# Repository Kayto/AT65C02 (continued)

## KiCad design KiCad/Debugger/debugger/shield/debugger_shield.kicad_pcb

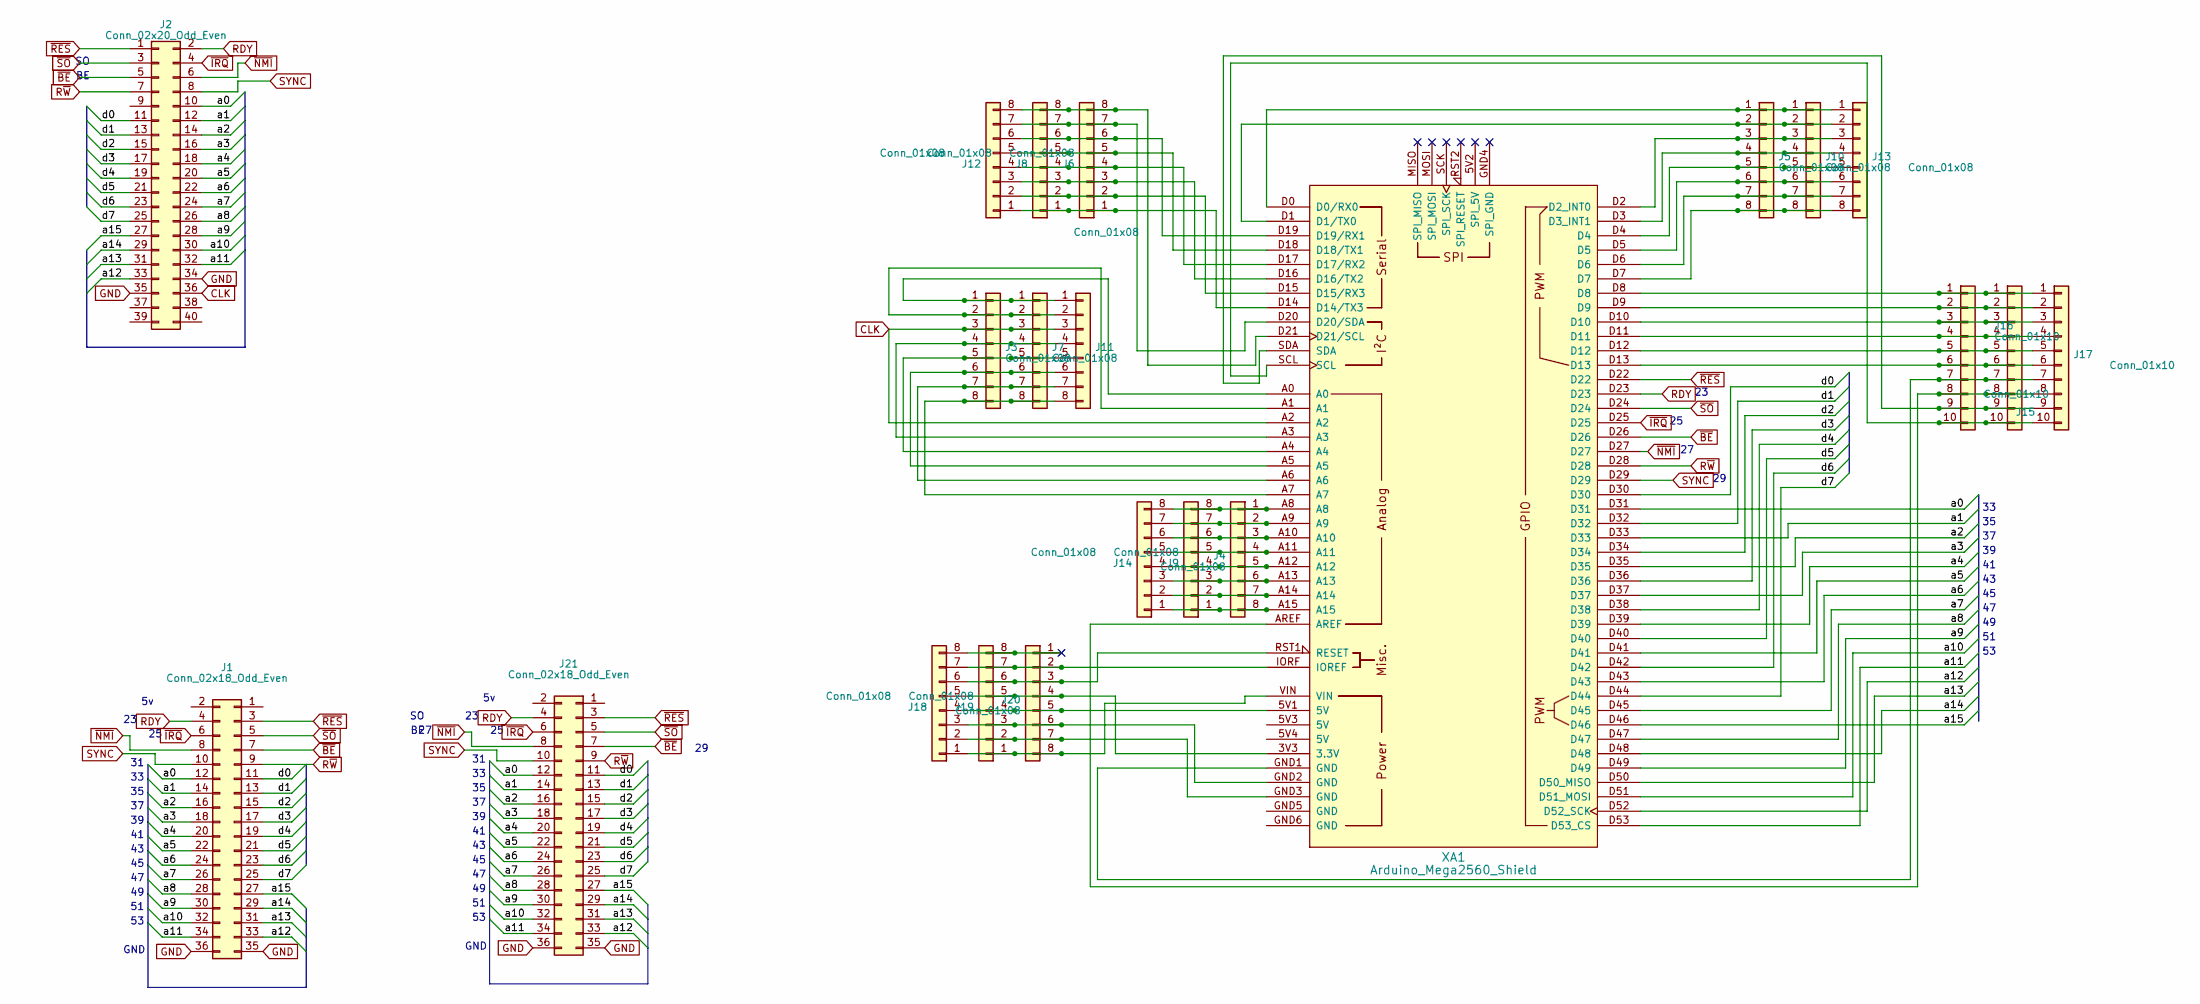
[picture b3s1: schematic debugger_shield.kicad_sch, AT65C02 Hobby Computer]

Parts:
J1: Conn_02x18_Odd_Even; PinHeader_2x18_P2.54mm_Vertical
J2: Conn_02x20_Odd_Even; IDC-Header_2x20_P2.54mm_Vertical
J3, J4, J5, J6, J11, J12, J13, J14, J18, J20: Conn_01x08; PinHeader_1x08_P2.54mm_Vertical
J7, J8, J9, J10, J19: Conn_01x08; PinSocket_1x08_P2.54mm_Vertical
J15, J17: Conn_01x10; PinHeader_1x10_P2.54mm_Vertical
J16: Conn_01x10; PinSocket_1x10_P2.54mm_Vertical
J21: Conn_02x18_Odd_Even; PinSocket_2x18_P2.54mm_Vertical
XA1: Arduino_Mega2560_Shield

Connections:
/a0: J1.12, J2.10, J21.12, XA1.D31
/a1: J1.14, J2.12, J21.14, XA1.D33
/a2: J1.16, J2.14, J21.16, XA1.D35
/a3: J1.18, J2.16, J21.18, XA1.D37
/a4: J1.20, J2.18, J21.20, XA1.D39
/a5: J1.22, J2.20, J21.22, XA1.D41
/a6: J1.24, J2.22, J21.24, XA1.D43
/a7: J1.26, J2.24, J21.26, XA1.D45
/a8: J1.28, J2.26, J21.28, XA1.D47
/a9: J1.30, J2.28, J21.30, XA1.D49
/a10: J1.32, J2.30, J21.32, XA1.D51 (D51_MOSI)
/a11: J1.34, J2.32, J21.34, XA1.D53 (D53_CS)
/a12: J1.33, J2.33, J21.33, XA1.D52 (D52_SCK)
/a13: J1.31, J2.31, J21.31, XA1.D50 (D50_MISO)
/a14: J1.29, J2.29, J21.29, XA1.D48
/a15: J1.27, J2.27, J21.27, XA1.D46
/d0: J1.11, J2.11, J21.11, XA1.D30
/d1: J1.13, J2.13, J21.13, XA1.D32
/d2: J1.15, J2.15, J21.15, XA1.D34
/d3: J1.17, J2.17, J21.17, XA1.D36
/d4: J1.19, J2.19, J21.19, XA1.D38
/d5: J1.21, J2.21, J21.21, XA1.D40
/d6: J1.23, J2.23, J21.23, XA1.D42
/d7: J1.25, J2.25, J21.25, XA1.D44
CLK: J2.36, J3.3, J7.3, J11.3, XA1.A2
GND: J1.35, J1.36, J2.34, J2.35, J21.35, J21.36
unnamed: J5.1, J10.1, J13.1, XA1.D0 (D0/RX0)
unnamed: J5.2, J10.2, J13.2, XA1.D1 (D1/TX0)
unnamed: J5.3, J10.3, J13.3, XA1.D2 (D2_INT0)
unnamed: J5.4, J10.4, J13.4, XA1.D3 (D3_INT1)
unnamed: J5.5, J10.5, J13.5, XA1.D4
unnamed: J5.6, J10.6, J13.6, XA1.D5
unnamed: J5.7, J10.7, J13.7, XA1.D6
unnamed: J5.8, J10.8, J13.8, XA1.D7
unnamed: J3.1, J7.1, J11.1, XA1.A0
unnamed: J3.2, J7.2, J11.2, XA1.A1
unnamed: J3.4, J7.4, J11.4, XA1.A3
unnamed: J3.5, J7.5, J11.5, XA1.A4
unnamed: J3.6, J7.6, J11.6, XA1.A5
unnamed: J3.7, J7.7, J11.7, XA1.A6
unnamed: J3.8, J7.8, J11.8, XA1.A7
unnamed: J6.1, J8.1, J12.1, XA1.D14 (D14/TX3)
unnamed: J6.2, J8.2, J12.2, XA1.D15 (D15/RX3)
unnamed: J6.3, J8.3, J12.3, XA1.D16 (D16/TX2)
unnamed: J6.4, J8.4, J12.4, XA1.D17 (D17/RX2)
unnamed: J6.5, J8.5, J12.5, XA1.D18 (D18/TX1)
unnamed: J6.6, J8.6, J12.6, XA1.D19 (D19/RX1)
unnamed: J6.7, J8.7, J12.7, XA1.D20 (D20/SDA)
unnamed: J6.8, J8.8, J12.8, XA1.D21 (D21/SCL)
unnamed: J4.8, J9.1, J14.1, XA1.A15
unnamed: J4.7, J9.2, J14.2, XA1.A14
unnamed: J4.6, J9.3, J14.3, XA1.A13
unnamed: J4.5, J9.4, J14.4, XA1.A12
unnamed: J4.4, J9.5, J14.5, XA1.A11
unnamed: J4.3, J9.6, J14.6, XA1.A10
unnamed: J4.2, J9.7, J14.7, XA1.A9
unnamed: J4.1, J9.8, J14.8, XA1.A8
unnamed: J15.1, J16.1, J17.1, XA1.D8
unnamed: J15.2, J16.2, J17.2, XA1.D9
unnamed: J15.3, J16.3, J17.3, XA1.D10
unnamed: J15.4, J16.4, J17.4, XA1.D11
unnamed: J15.5, J16.5, J17.5, XA1.D12
unnamed: J15.6, J16.6, J17.6, XA1.D13
unnamed: J15.7, J16.7, J17.7, XA1.GND1 (GND)
unnamed: J15.8, J16.8, J17.8, XA1.AREF
unnamed: J15.9, J16.9, J17.9, XA1.SDA
unnamed: J15.10, J16.10, J17.10, XA1.SCL
unnamed: J18.1, J19.1, J20.8, XA1.VIN
unnamed: J18.2, J19.2, J20.7, XA1.GND3 (GND)
unnamed: J18.3, J19.3, J20.6, XA1.GND2 (GND)
unnamed: J18.4, J19.4, J20.5, XA1.5V1 (5V)
unnamed: J18.5, J19.5, J20.4, XA1.3V3 (3.3V)
unnamed: J18.6, J19.6, J20.3, XA1.RST1 (RESET)
unnamed: J18.7, J19.7, J20.2, XA1.IORF (IOREF)
RDY: J1.4, J2.2, J21.4, XA1.D23
R~W: J1.9, J2.7, J21.9, XA1.D28
SYNC: J1.10, J2.8, J21.10, XA1.D29
~BE: J1.7, J2.5, J21.7, XA1.D26
~IRQ: J1.6, J2.4, J21.6, XA1.D25
~NMI: J1.8, J2.6, J21.8, XA1.D27
~RES: J1.3, J2.1, J21.3, XA1.D22
~SO: J1.5, J2.3, J21.5, XA1.D24

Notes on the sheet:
GND

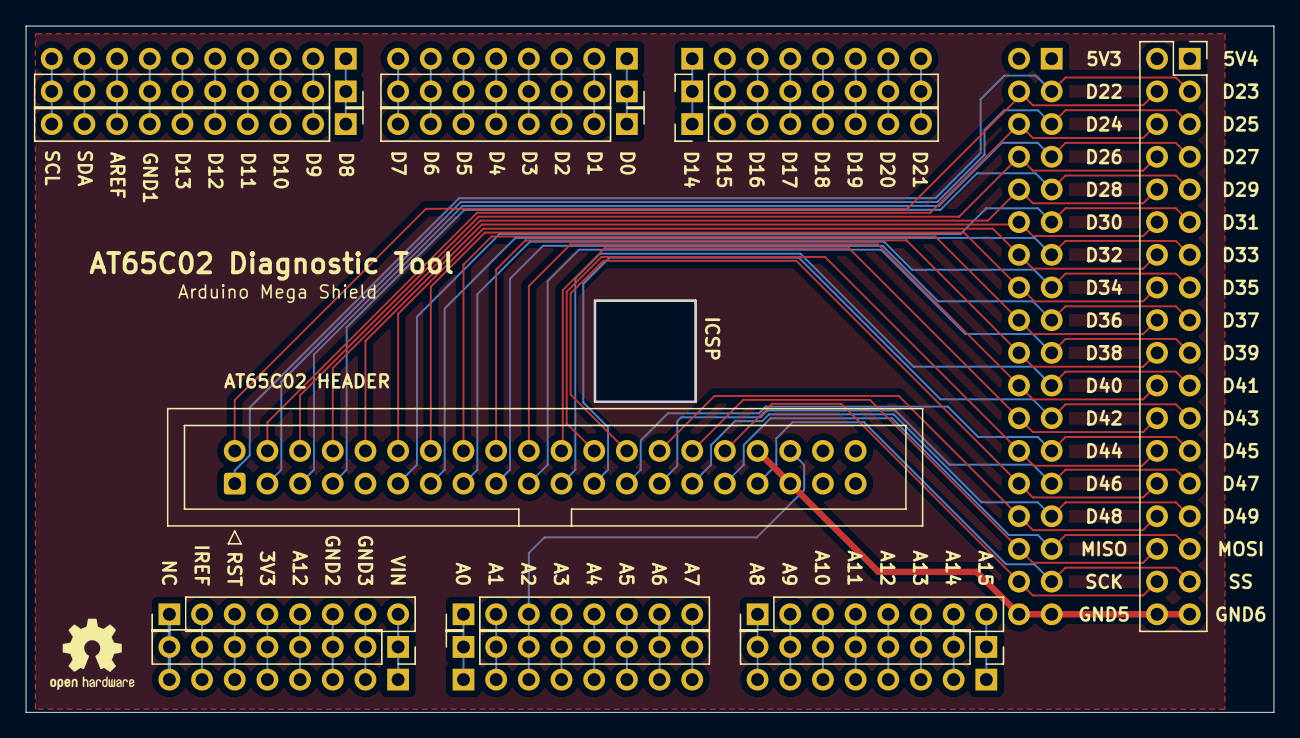
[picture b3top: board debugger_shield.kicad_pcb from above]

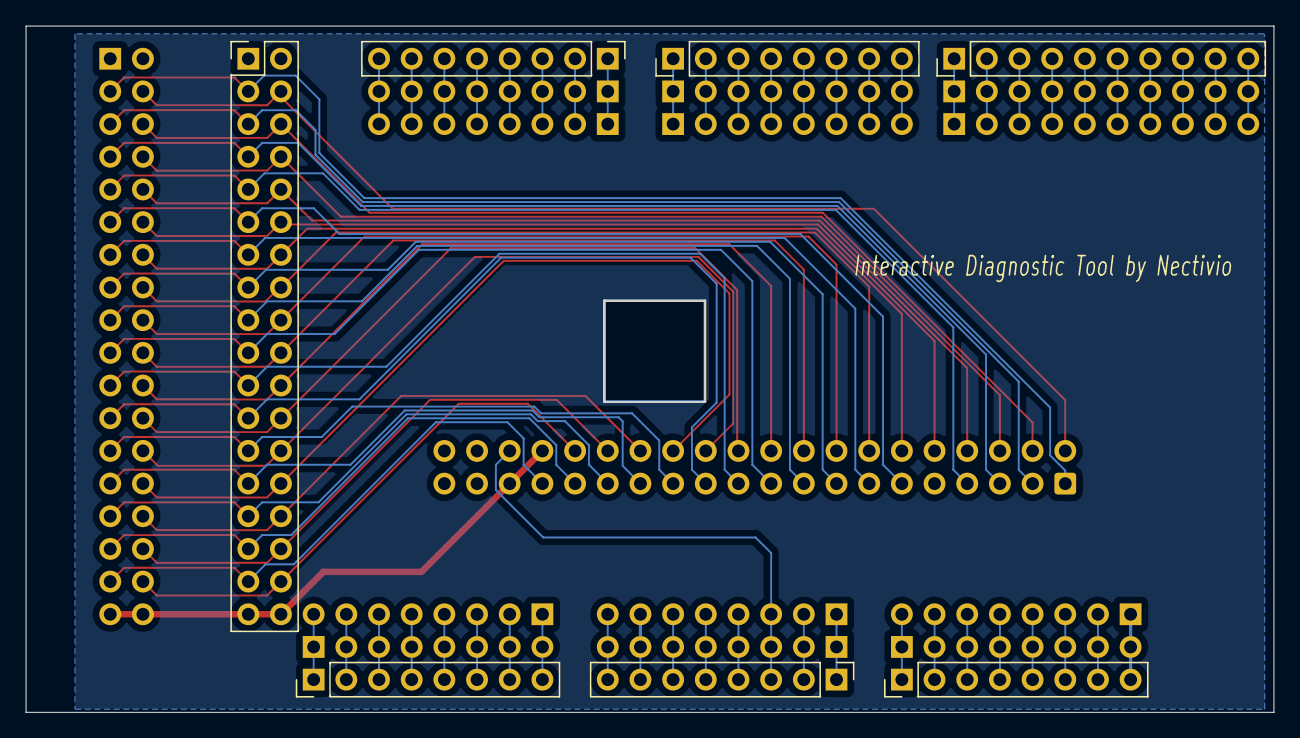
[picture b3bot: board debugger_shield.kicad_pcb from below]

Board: 2 copper layers, 97.0 x 53.3 mm, 21 parts (7 on the bottom side), 82 nets.

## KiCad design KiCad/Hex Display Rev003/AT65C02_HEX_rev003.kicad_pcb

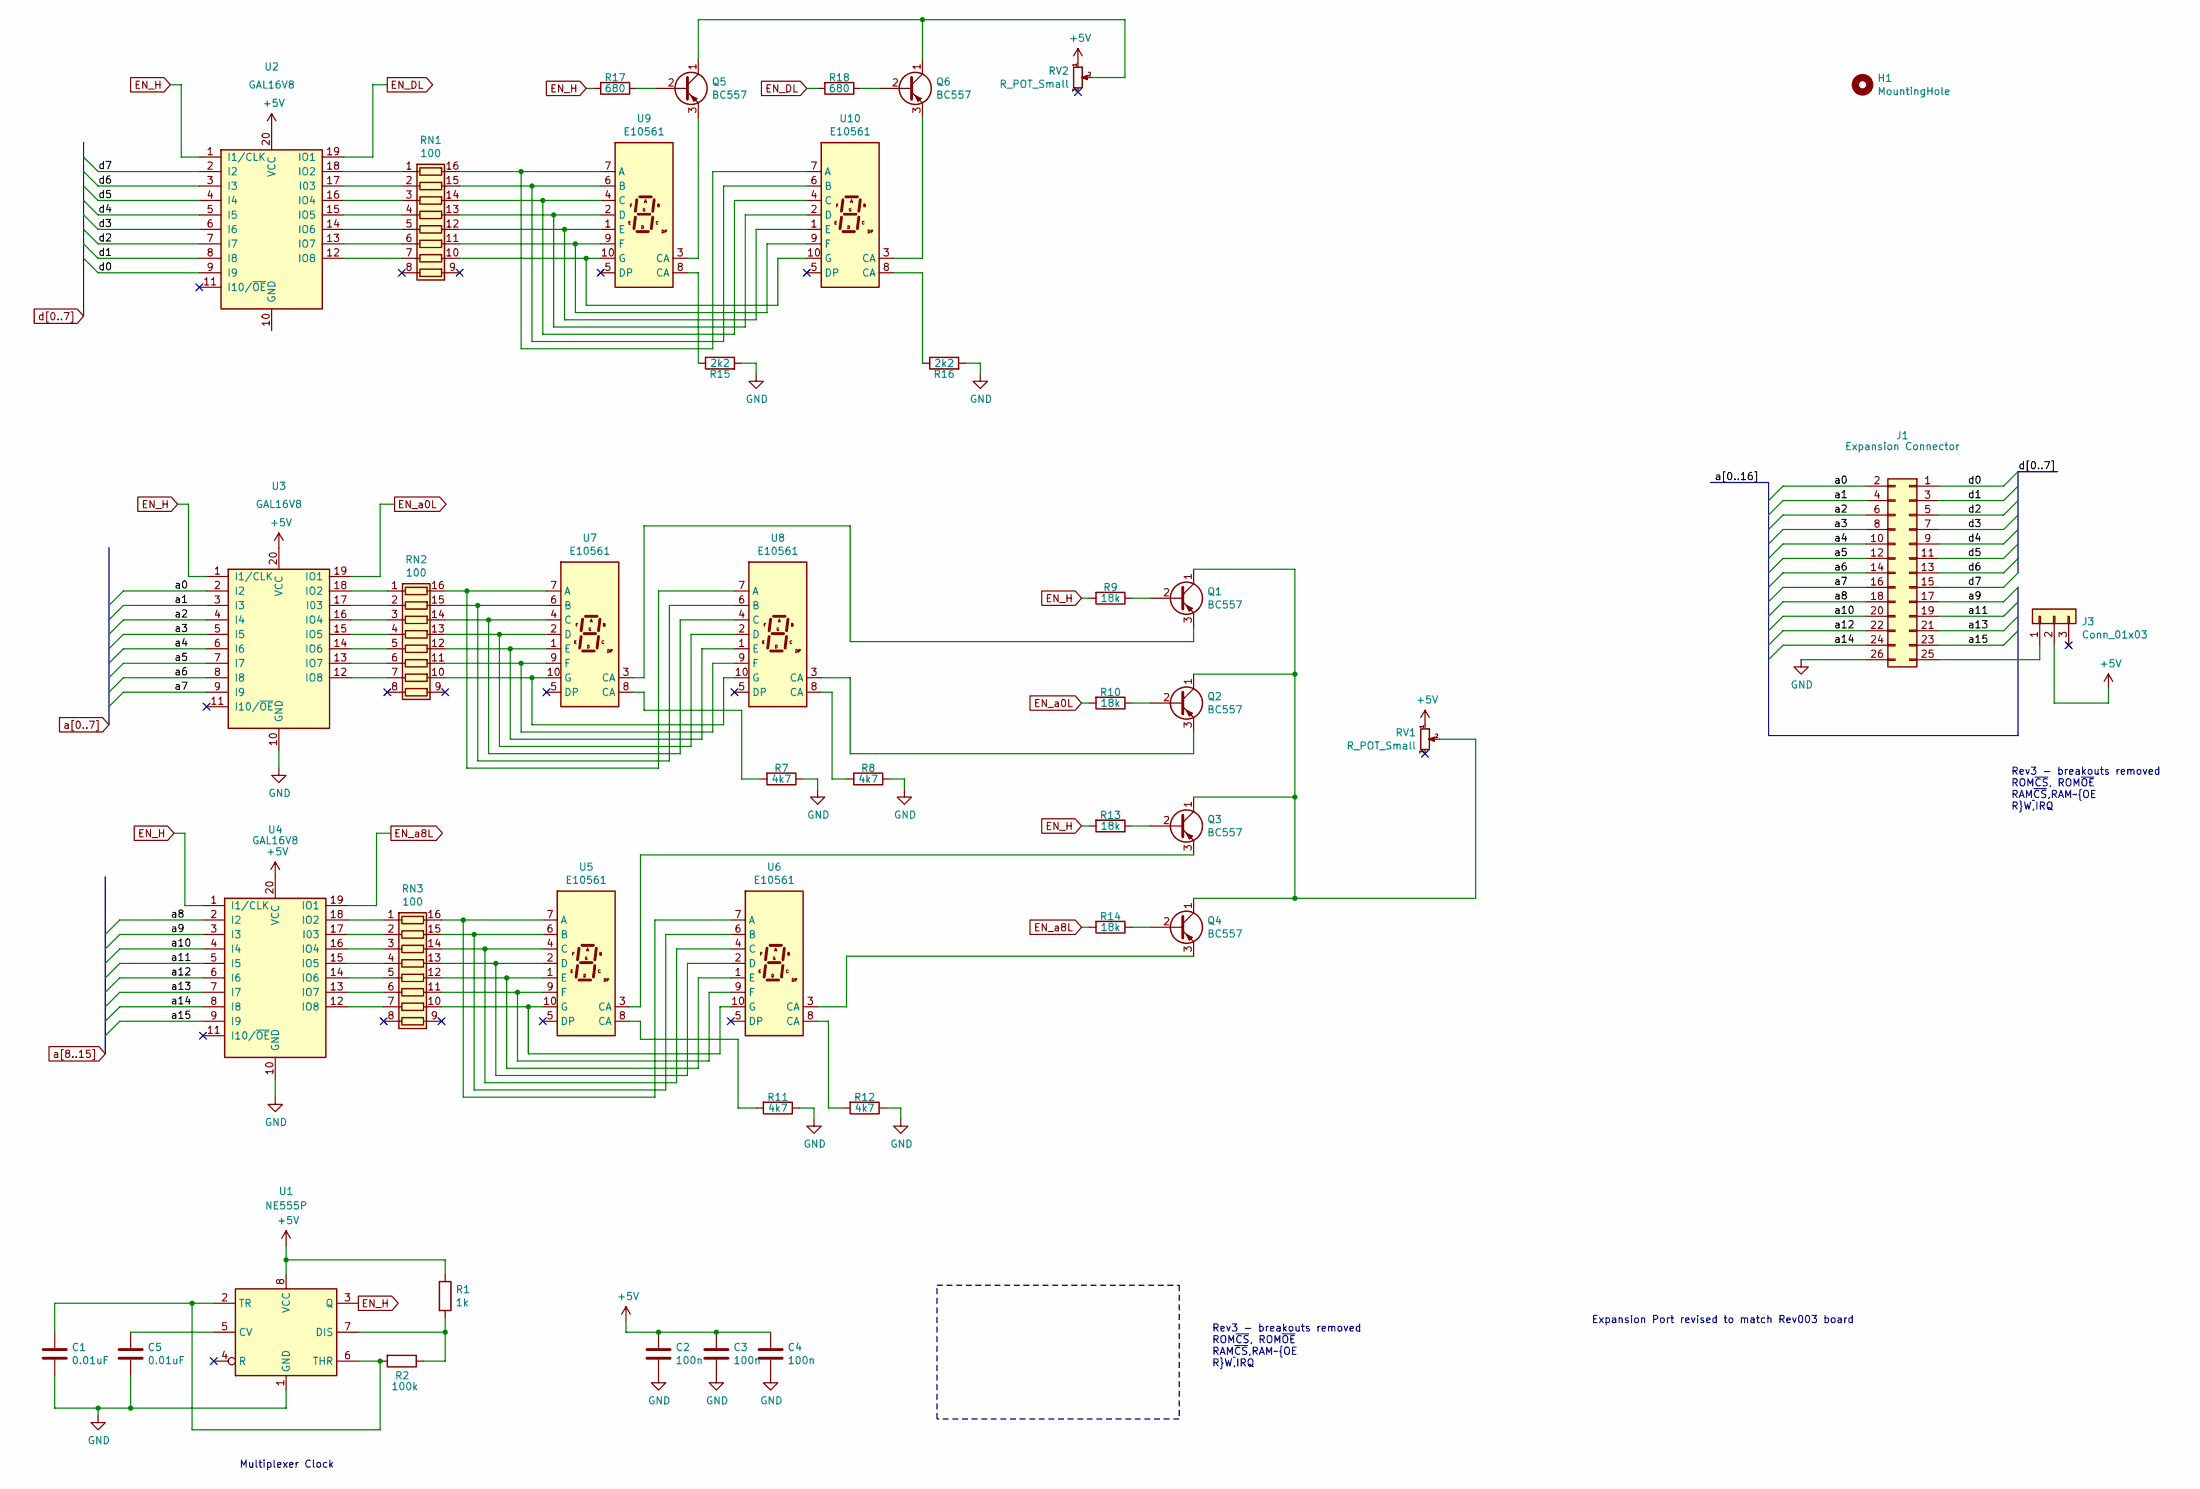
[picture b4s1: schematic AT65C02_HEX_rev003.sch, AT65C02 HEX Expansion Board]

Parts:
C1, C5: 0.01uF; C_Disc_D5.0mm_W2.5mm_P5.00mm
C2, C3, C4: 100n; C_Disc_D5.0mm_W2.5mm_P5.00mm
H1: MountingHole; MountingHole_2.2mm_M2
J1: Expansion Connector; PinHeader_2x13_P2.54mm_Vertical
J3: Conn_01x03; PinHeader_1x03_P2.54mm_Vertical
Q1, Q2, Q3, Q4, Q5, Q6: BC557; TO-92_Inline
R1: 1k; R_Axial_DIN0207_L6.3mm_D2.5mm_P7.62mm_Horizontal
R2: 100k; R_Axial_DIN0207_L6.3mm_D2.5mm_P7.62mm_Horizontal
R7, R8, R11, R12: 4k7; R_Axial_DIN0207_L6.3mm_D2.5mm_P7.62mm_Horizontal
R9, R10, R13, R14: 18k; R_Axial_DIN0207_L6.3mm_D2.5mm_P7.62mm_Horizontal
R15, R16: 2k2; R_Axial_DIN0207_L6.3mm_D2.5mm_P7.62mm_Horizontal
R17, R18: 680; R_Axial_DIN0207_L6.3mm_D2.5mm_P7.62mm_Horizontal
RN1, RN2, RN3: 100; DIP-16_W7.62mm_Socket
RV1, RV2: R_POT_Small; Potentiometer_Piher_PT-10-V10_Vertical
U1: NE555P; DIP-8_W7.62mm_Socket
U2, U3, U4: GAL16V8; DIP-20_W7.62mm_Socket
U5, U6, U7, U8, U9, U10: E10561; 7SegmentLED_LTS6760_LTS6780

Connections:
+5V: C2.1, C3.1, C4.1, J3.2, R1.1, RV1.1, RV2.1, U1.8 (VCC), U2.20 (VCC), U3.20 (VCC), U4.20 (VCC)
EN_DL: R18.2, U2.19 (IO1)
EN_H: R9.2, R13.2, R17.2, U1.3 (Q), U2.1 (I1/CLK), U3.1 (I1/CLK), U4.1 (I1/CLK)
EN_a0L: R10.2, U3.19 (IO1)
EN_a8L: R14.2, U4.19 (IO1)
GND: C1.2, C2.2, C3.2, C4.2, C5.2, J1.26, R7.1, R8.1, R11.1, R12.1, R15.2, R16.2, U1.1 (GND), U3.10 (GND), U4.10 (GND)
unnamed: C1.1, R2.2, U1.2 (TR), U1.6 (THR)
unnamed: C5.1, U1.5 (CV)
unnamed: J1.25, J3.1
unnamed: Q1.1 (C), Q2.1 (C), Q3.1 (C), Q4.1 (C), RV1.2
unnamed: Q1.2 (B), R9.1
unnamed: Q1.3 (E), U7.3 (CA)
unnamed: Q2.2 (B), R10.1
unnamed: Q2.3 (E), U8.3 (CA)
unnamed: Q3.2 (B), R13.1
unnamed: Q3.3 (E), U5.3 (CA)
unnamed: Q4.2 (B), R14.1
unnamed: Q4.3 (E), U6.3 (CA)
unnamed: Q5.1 (C), Q6.1 (C), RV2.2
unnamed: Q5.2 (B), R17.1
unnamed: Q5.3 (E), U9.3 (CA)
unnamed: Q6.2 (B), R18.1
unnamed: Q6.3 (E), U10.3 (CA)
unnamed: R1.2, R2.1, U1.7 (DIS)
unnamed: R7.2, U7.8 (CA)
unnamed: R8.2, U8.8 (CA)
unnamed: R11.2, U5.8 (CA)
unnamed: R12.2, U6.8 (CA)
unnamed: R15.1, U9.8 (CA)
unnamed: R16.1, U10.8 (CA)
unnamed: RN1.1 (R1.1), U2.18 (IO2)
unnamed: RN1.2 (R2.1), U2.17 (I03)
unnamed: RN1.3 (R3.1), U2.16 (IO4)
unnamed: RN1.4 (R4.1), U2.15 (IO5)
unnamed: RN1.5 (R5.1), U2.14 (IO6)
unnamed: RN1.6 (R6.1), U2.13 (IO7)
unnamed: RN1.7 (R7.1), U2.12 (IO8)
unnamed: RN1.10 (R7.2), U9.10 (G), U10.10 (G)
unnamed: RN1.11 (R6.2), U9.9 (F), U10.9 (F)
unnamed: RN1.12 (R5.2), U9.1 (E), U10.1 (E)
unnamed: RN1.13 (R4.2), U9.2 (D), U10.2 (D)
unnamed: RN1.14 (R3.2), U9.4 (C), U10.4 (C)
unnamed: RN1.15 (R2.2), U9.6 (B), U10.6 (B)
unnamed: RN1.16 (R1.2), U9.7 (A), U10.7 (A)
unnamed: RN2.1 (R1.1), U3.18 (IO2)
unnamed: RN2.2 (R2.1), U3.17 (I03)
unnamed: RN2.3 (R3.1), U3.16 (IO4)
unnamed: RN2.4 (R4.1), U3.15 (IO5)
unnamed: RN2.5 (R5.1), U3.14 (IO6)
unnamed: RN2.6 (R6.1), U3.13 (IO7)
unnamed: RN2.7 (R7.1), U3.12 (IO8)
unnamed: RN2.10 (R7.2), U7.10 (G), U8.10 (G)
unnamed: RN2.11 (R6.2), U7.9 (F), U8.9 (F)
unnamed: RN2.12 (R5.2), U7.1 (E), U8.1 (E)
unnamed: RN2.13 (R4.2), U7.2 (D), U8.2 (D)
unnamed: RN2.14 (R3.2), U7.4 (C), U8.4 (C)
unnamed: RN2.15 (R2.2), U7.6 (B), U8.6 (B)
unnamed: RN2.16 (R1.2), U7.7 (A), U8.7 (A)
unnamed: RN3.1 (R1.1), U4.18 (IO2)
unnamed: RN3.2 (R2.1), U4.17 (I03)
unnamed: RN3.3 (R3.1), U4.16 (IO4)
unnamed: RN3.4 (R4.1), U4.15 (IO5)
unnamed: RN3.5 (R5.1), U4.14 (IO6)
unnamed: RN3.6 (R6.1), U4.13 (IO7)
unnamed: RN3.7 (R7.1), U4.12 (IO8)
unnamed: RN3.10 (R7.2), U5.10 (G), U6.10 (G)
unnamed: RN3.11 (R6.2), U5.9 (F), U6.9 (F)
unnamed: RN3.12 (R5.2), U5.1 (E), U6.1 (E)
unnamed: RN3.13 (R4.2), U5.2 (D), U6.2 (D)
unnamed: RN3.14 (R3.2), U5.4 (C), U6.4 (C)
unnamed: RN3.15 (R2.2), U5.6 (B), U6.6 (B)
unnamed: RN3.16 (R1.2), U5.7 (A), U6.7 (A)
a0: J1.2, U3.2 (I2)
a1: J1.4, U3.3 (I3)
a2: J1.6, U3.4 (I4)
a3: J1.8, U3.5 (I5)
a4: J1.10, U3.6 (I6)
a5: J1.12, U3.7 (I7)
a6: J1.14, U3.8 (I8)
a7: J1.16, U3.9 (I9)
a8: J1.18, U4.2 (I2)
a9: J1.17, U4.3 (I3)
a10: J1.20, U4.4 (I4)
a11: J1.19, U4.5 (I5)
a12: J1.22, U4.6 (I6)
a13: J1.21, U4.7 (I7)
a14: J1.24, U4.8 (I8)
a15: J1.23, U4.9 (I9)
d0: J1.1, U2.9 (I9)
d1: J1.3, U2.8 (I8)
d2: J1.5, U2.7 (I7)
d3: J1.7, U2.6 (I6)
d4: J1.9, U2.5 (I5)
d5: J1.11, U2.4 (I4)
d6: J1.13, U2.3 (I3)
d7: J1.15, U2.2 (I2)

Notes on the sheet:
Expansion Port revised to match Rev003 board
Multiplexer Clock
Rev3 - breakouts removed ROM~CS~, ROM~OE~ RAM~CS~,RAM~OE R~W~,~IRQ~

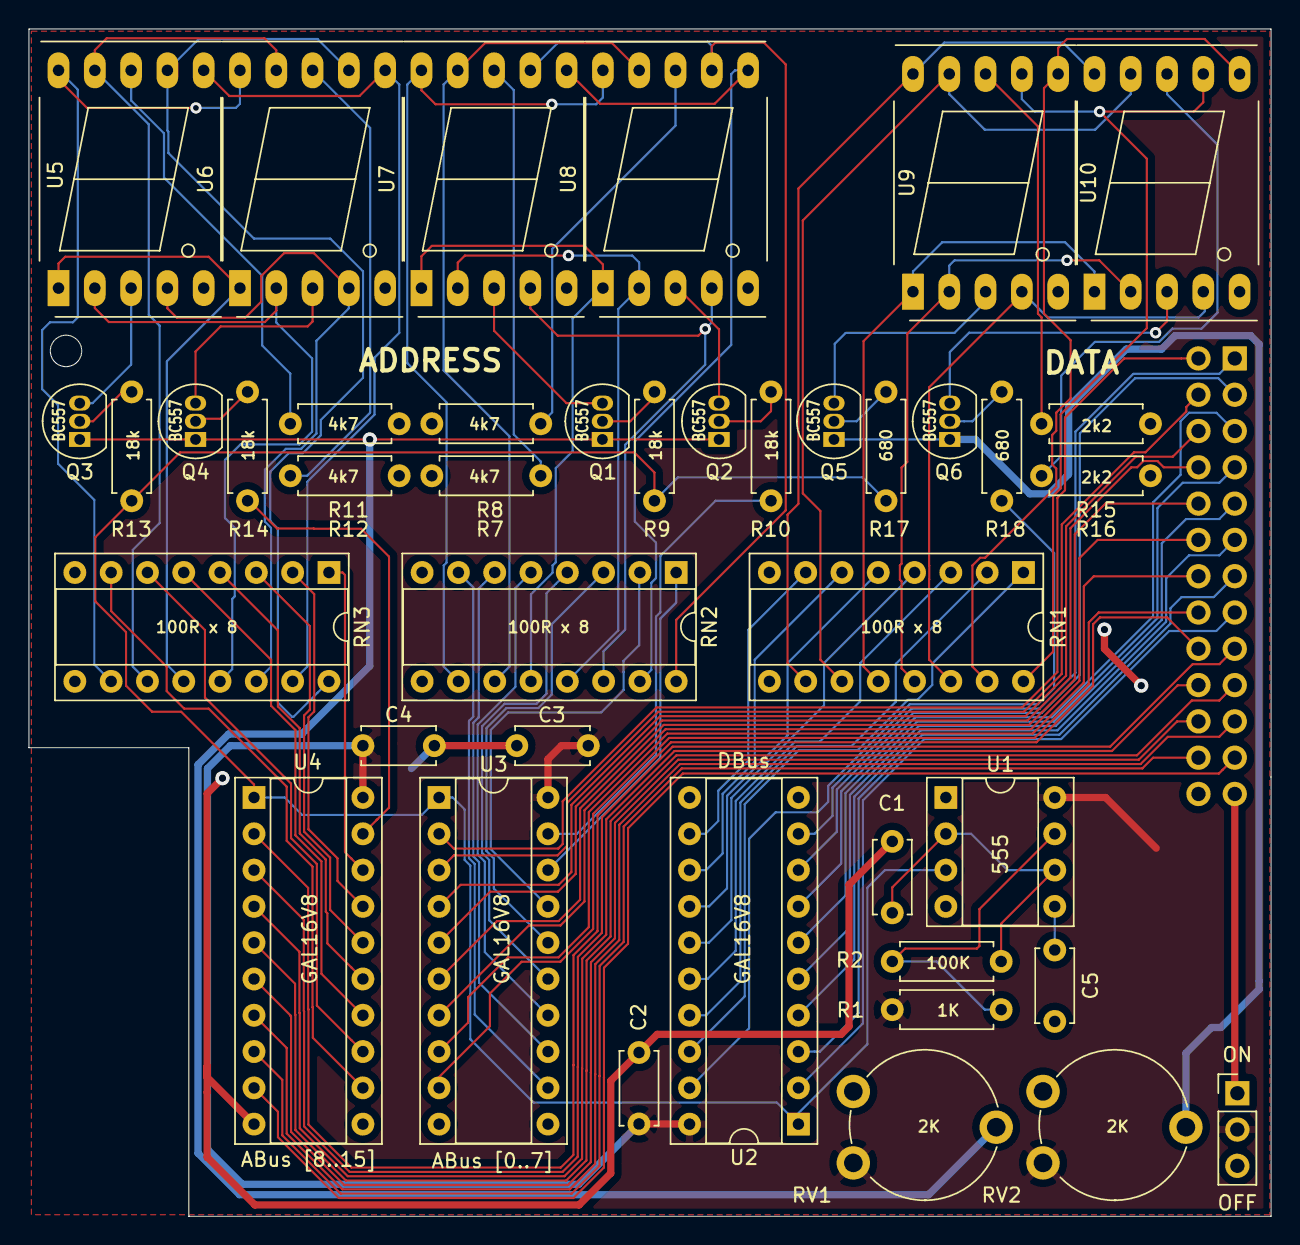
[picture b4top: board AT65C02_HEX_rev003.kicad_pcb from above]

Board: 2 copper layers, 86.9 x 83.1 mm, 43 parts (1 on the bottom side), 96 nets.

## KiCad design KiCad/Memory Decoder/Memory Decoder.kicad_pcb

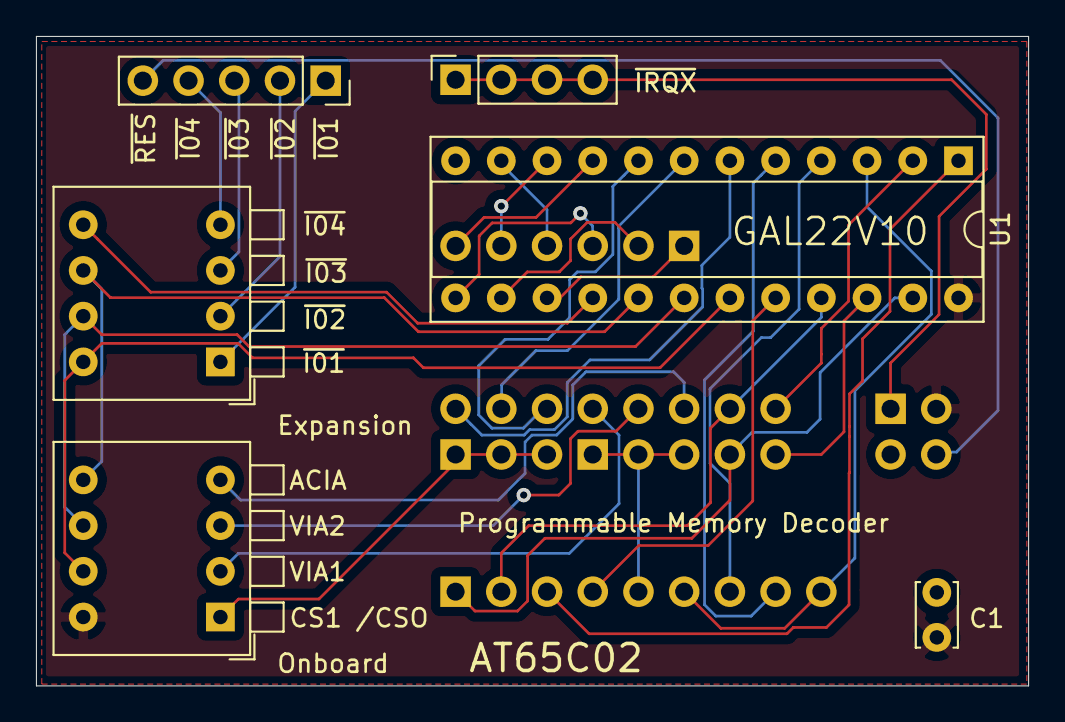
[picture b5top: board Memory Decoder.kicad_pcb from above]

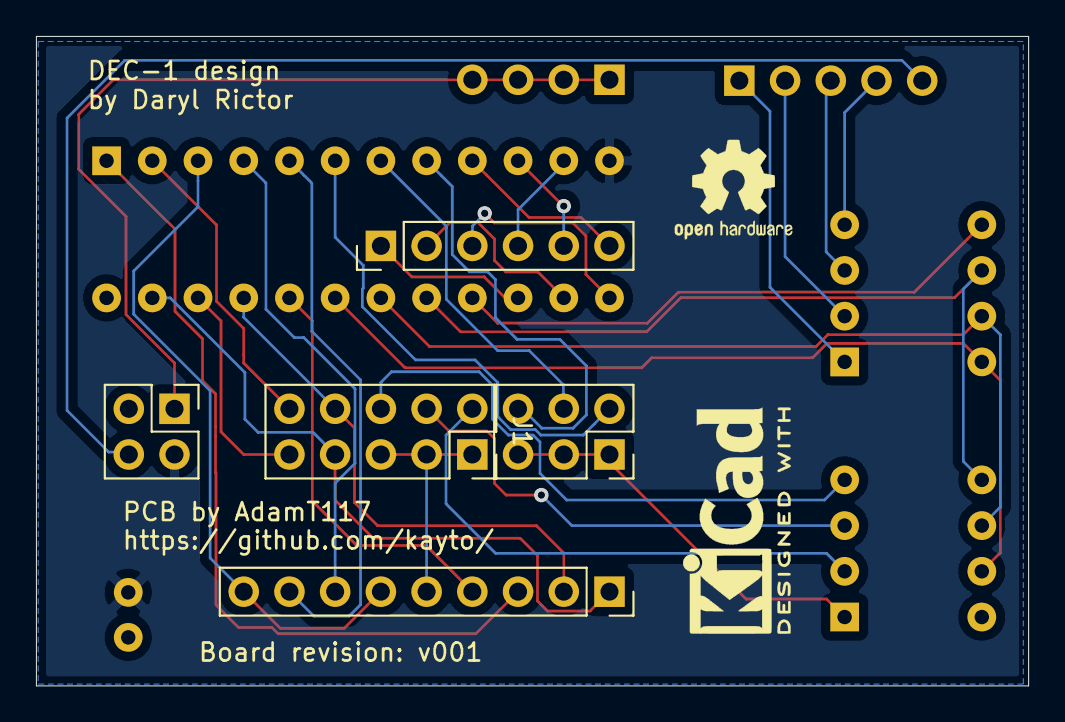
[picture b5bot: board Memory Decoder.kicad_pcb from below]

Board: 2 copper layers, 55.1 x 36.1 mm, 11 parts (5 on the bottom side), 35 nets.

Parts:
C1: 0.1uF; C_Disc_D3.4mm_W2.1mm_P2.50mm
J1: IOCS/Decoder Signals Expansion #5; PinSocket_2x05_P2.54mm_Vertical
J2: Conn_02x02_Odd_Even; PinHeader_2x02_P2.54mm_Vertical
J3: Decoder Signals; PinSocket_1x09_P2.54mm_Vertical
J4: Conn_02x03_Odd_Even; PinSocket_2x03_P2.54mm_Vertical
J5: Memory Decoder Expansion; PinHeader_1x06_P2.54mm_Vertical
J6: ~CS1~; PinSocket_1x05_P2.54mm_Vertical
J7: ~CS1~; PinSocket_1x04_P2.54mm_Vertical
SW1, SW2: SW_DIP_x04; SW_DIP_SPSTx04_Piano_10.8x11.72mm_W7.62mm_P2.54mm
U1: Flexible Memory Decoder; DIP-24_W7.62mm_Socket

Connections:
+5V: C1.1, J2.3, SW1.8, U1.24
/a4: J5.1, U1.15
/a5: J5.2, U1.14
/a6: J5.3, U1.13
/a7: J5.4, U1.11
/a8: J5.5, U1.10
/a9: J5.6, U1.9
/a10: J4.6, U1.8
/a11: J4.4, U1.7
/a12: J4.2, U1.6
/a13: J3.8, U1.5
/a14: J3.7, U1.4
/a15: J3.6, J3.9, U1.3
A_CSO: J4.1, J4.3, J4.5, SW1.1
CLK: J3.3, U1.1
GND: C1.2, J2.2, U1.12
RAM~WE: J1.9, U1.22
R~W: J1.10, U1.2
~IO1: SW1.7, SW2.8, U1.19
~IO1x: J6.1, SW2.1
~IO2: SW1.6, SW2.7, U1.18
~IO2x: J6.2, SW2.2
~IO3: SW1.5, SW2.6, U1.17
~IO3x: J6.3, SW2.3
~IO4: SW2.5, U1.16
~IO4x: J6.4, SW2.4
~IOCS: J1.1, J1.3, J1.5, J3.5
~IOCS_A: J1.6, SW1.4
~IOCS_V1: J1.2, SW1.2
~IOCS_V2: J1.4, SW1.3
~IRQX: J2.1, J7.1, J7.2, J7.3, J7.4
~RAM_CS: J1.8, J3.2, U1.21
~RAM_OE: J1.7, J3.1, U1.23
~RES: J2.4, J6.5
~ROM_CS: J3.4, U1.20

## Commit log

2022-11-09 Initial Release
2022-11-15 Rev001 Publish - Rev002 WIP
    General folder tidy. Rev001 tidied to publish. Rev002 WIP.
2022-11-15 Rev001 Gerbers added
2022-11-15 Silk Screen Modifications - Hex Display WIP
2022-11-15 Hex Display Updates WIP
2022-12-02 HEX Board Mods
    Hex board changes. Main board Hex to Latches
2022-12-05 release revisions
    REv001,002 and HEX
2023-03-14 rev003 started
2023-03-15 Update fp-info-cache
2023-03-15 schematic updates
2023-03-31 rev003
2023-03-31 kicad gitignore
2023-03-31 Rev003 tidy
2023-03-31 clean old revs
2023-03-31 Create LICENSE
2023-03-31 gitignore
2023-04-05 PDF Schematic Added
2023-04-05 BOM added
2023-04-05 Images added
2023-04-05 Gerbers Added
2023-04-05 Pads changed
2023-04-19 Image added
2023-04-19 memory decoder revised
2023-05-01 Silkscreen updates
2023-05-01 U8 ZIF socket
2023-05-01 ZIF Gerbers added
2023-05-02 Typos in README.
2023-05-02 Latest News Update
2023-05-09 Rev004 WIP updates
    Work in Progress
2023-05-09 BOM update
2023-05-09 HEX board Rev003
2023-05-10 Rev004 revisions
2023-05-10 Rev004 updates
2023-05-22 debugger wip
2023-05-22 silkscreen black and white
2023-06-01 Hex board Resistor value update
2023-06-01 Hex Board BOM update
2023-06-12 Code Added
2023-06-12 Code Updates
2023-06-12 Update LICENSE
2023-06-12 License Updates
2023-06-17 readme update
2023-06-19 software added
2023-06-21 smon6502 added
2023-06-22 Image update
2023-06-25 Update smon.s
    'fixed'CR. added credits
2023-07-16 SYSMon65 binary added
2023-08-06 minor PCB revisions
2023-08-06 Minor PCB updates
2023-08-23 Jumper explanation added
2023-08-23 jumper image added
2024-06-06 Delete Software/ATOS1 directory
    WIP removed from Public
2024-06-06 Delete KiCad/Debugger directory
    WIP removed from Public
2025-05-29 Refresh 2025
    No changes just a refresh and update to readme.
2025-05-29 Refresh 2025
    Just an update to the readme with a few potential ideas.
2025-12-15 ATOS Software added
    ATOS release
2025-12-15 Fix link path for Software_ATOS in README.md
2025-12-15 Fix typo in Software_ATOS link in README
2025-12-15 Update links in README for Software_ATOS
